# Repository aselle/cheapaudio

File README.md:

# CheapAudio

## Introduction

The purpose of this project is to create a set of hardware and software that allows you to do your own speakers that involve active crossovers.

Software is extremely rough, mostly used for my own purposes. Use at your own risk, what contributions are welcome. 

## Components

### Hardware

#### CheapDSP - ADAU1701 based DSP board

#### CheapAMP - TI TAS 5754M Amp

#### CheapSPDIF - SPDIF to i2s supported by wolfsen chip

One thing that I've done uniquely with these is that I have used skidl to design the circuit using python script. This has the downside that there is no hardware schematic, only a PCB layout.

### Software
  * dspserver - A server that runs on a esp8266 that allows you to upload new firmwares for your DSP, control volume, etc. It also implements Sigma Studio TCP/IP interface so you can use the Sigma Studio tools w/o the USB interface
  * React - The start of an interface for manipulating the DSP through the web
  * Tools - Utility scripts to convert various SigmaStudio 
  * Measuring - NumPy script that can measure response curve from calibrated Microphone

Apache header:

    Copyright 2022 Andrew Selle

    Licensed under the Apache License, Version 2.0 (the "License");
    you may not use this file except in compliance with the License.
    You may obtain a copy of the License at

        https://www.apache.org/licenses/LICENSE-2.0

    Unless required by applicable law or agreed to in writing, software
    distributed under the License is distributed on an "AS IS" BASIS,
    WITHOUT WARRANTIES OR CONDITIONS OF ANY KIND, either express or implied.
    See the License for the specific language governing permissions and
    limitations under the License.

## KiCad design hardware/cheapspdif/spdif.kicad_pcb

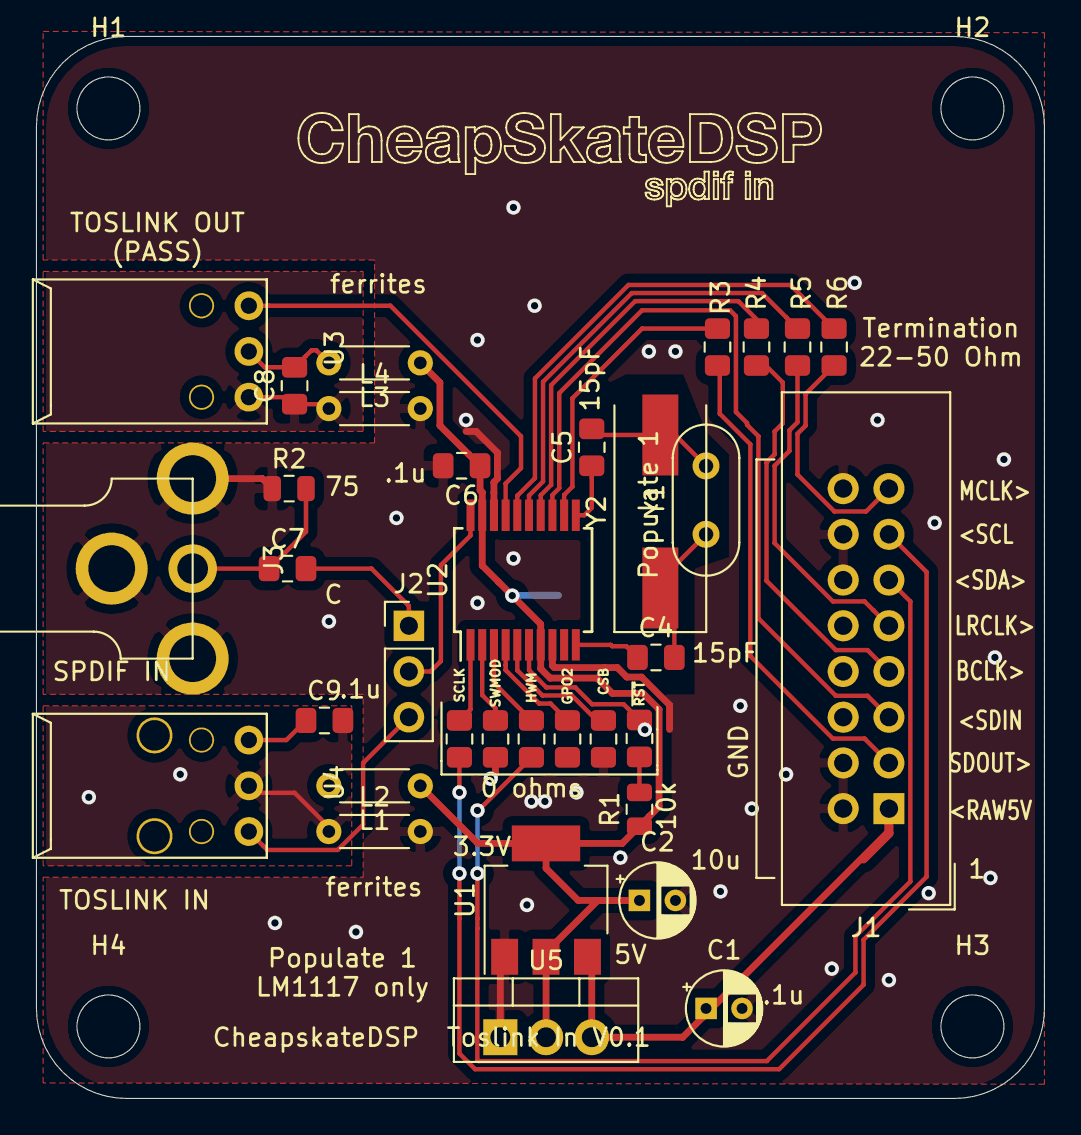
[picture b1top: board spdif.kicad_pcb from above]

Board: 2 copper layers, 56.0 x 59.0 mm, 39 parts (1 on the bottom side), 34 nets.

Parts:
C1: .1u; CP_Radial_D4.0mm_P2.00mm
C2: 10u; CP_Radial_D4.0mm_P2.00mm
C3: 1u; C_0805_2012Metric_Pad1.15x1.40mm_HandSolder
C4, C5: 15pF; C_0805_2012Metric_Pad1.15x1.40mm_HandSolder
C6, C8, C9: .1u; C_0805_2012Metric_Pad1.15x1.40mm_HandSolder
C7: C; C_0805_2012Metric_Pad1.15x1.40mm_HandSolder
H1, H2, H3, H4: MountingHole; MountingHole_3.5mm
J1: Conn_02x08_Odd_Even; IDC-Header_2x08_P2.54mm_Vertical
J2: Conn_01x03_Male; PinHeader_1x03_P2.54mm_Vertical
J3: Conn_Coaxial; RCJ-017-RCA
L1, L2, L3, L4: 47uH; R_Axial_DIN0204_L3.6mm_D1.6mm_P5.08mm_Horizontal
R1: 10k; R_0805_2012Metric
R2: 75; R_0805_2012Metric
R3, R4, R5, R6: 22; R_0805_2012Metric_Pad1.15x1.40mm_HandSolder
R7, R8, R9, R10, R11, R12: 0; R_0805_2012Metric_Pad1.15x1.40mm_HandSolder
U1: LD1117S12TR_SOT223; SOT-223-3_TabPin2
U2: wm8804; SSOP-20_5.3x7.2mm_P0.65mm
U3: PLT135_T8; PLT133-T10
U4: PLR135_T8; PLR135-T8
U5: LM1117-3.3; TO-220-3_Vertical
Y1: 12.288MHz; Crystal_HC52-8mm_Vertical
Y2: 12.288MHz; Crystal_SMD_HC49-SD

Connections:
+3V3: C2.1, C3.1, C6.1, L1.1, L3.1, R1.1, U1.2, U2.7, U2.19, U5.2
/BCLK: R4.2, U2.14
/COAXIN_DATA: J2.3, U4.1
/CSB: R11.1, U2.5
/GPO2: R10.1, U2.4
/HWMODE: R9.1, U2.3
/LRCLK: R5.2, U2.15
/MCLK: R6.2, U2.16
/RAW5V: C1.1, J1.1, U1.3, U5.3
/RX0: J2.2, U2.20
/SCL: J1.13, R7.2
/SCLK: R7.1, U2.1
/SDA: J1.11, R9.2
/SD_FROM_DSP: J1.5, U2.13
/SD_TO_DSP: R3.2, U2.12
/SWIFMODE: R8.1, U2.2
/TOSIN_3V3: C9.1, L1.2, U4.3
/TOSIN_GND: C9.2, L2.1, U4.2
/TOUT_GND: C8.1, L4.1, U3.3
/TOUT_VCC: C8.2, L3.2, U3.2
/XIN: C5.1, U2.11
/XOP: C4.1, U2.10
/~RESET: R1.2, R12.2
/~RESETB: R12.1, U2.6
GND: C1.2, C2.2, C3.2, C6.2, J1.2, J1.4, J1.6, J1.8, J1.10, J1.12, J1.14, J1.16, J3.2, L2.2, L4.2, R2.1, R8.2, R11.2, U1.1, U2.8, U2.18, U5.1
unnamed: C4.2, Y1.1, Y2.1
unnamed: C5.2, Y1.2, Y2.2
unnamed: C7.1, J3.1, R2.2
unnamed: C7.2, J2.1
unnamed: J1.3, R3.1
unnamed: J1.7, R4.1
unnamed: J1.9, R5.1
unnamed: J1.15, R6.1
unnamed: U2.17, U3.1

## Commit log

2022-03-07 Initial cheapskate audio commit.
2022-03-07 iamgery in docs
2024-12-20 Latest firmware and software
2025-02-21 add firmware
2025-02-21 latest
2025-03-15 latest software
